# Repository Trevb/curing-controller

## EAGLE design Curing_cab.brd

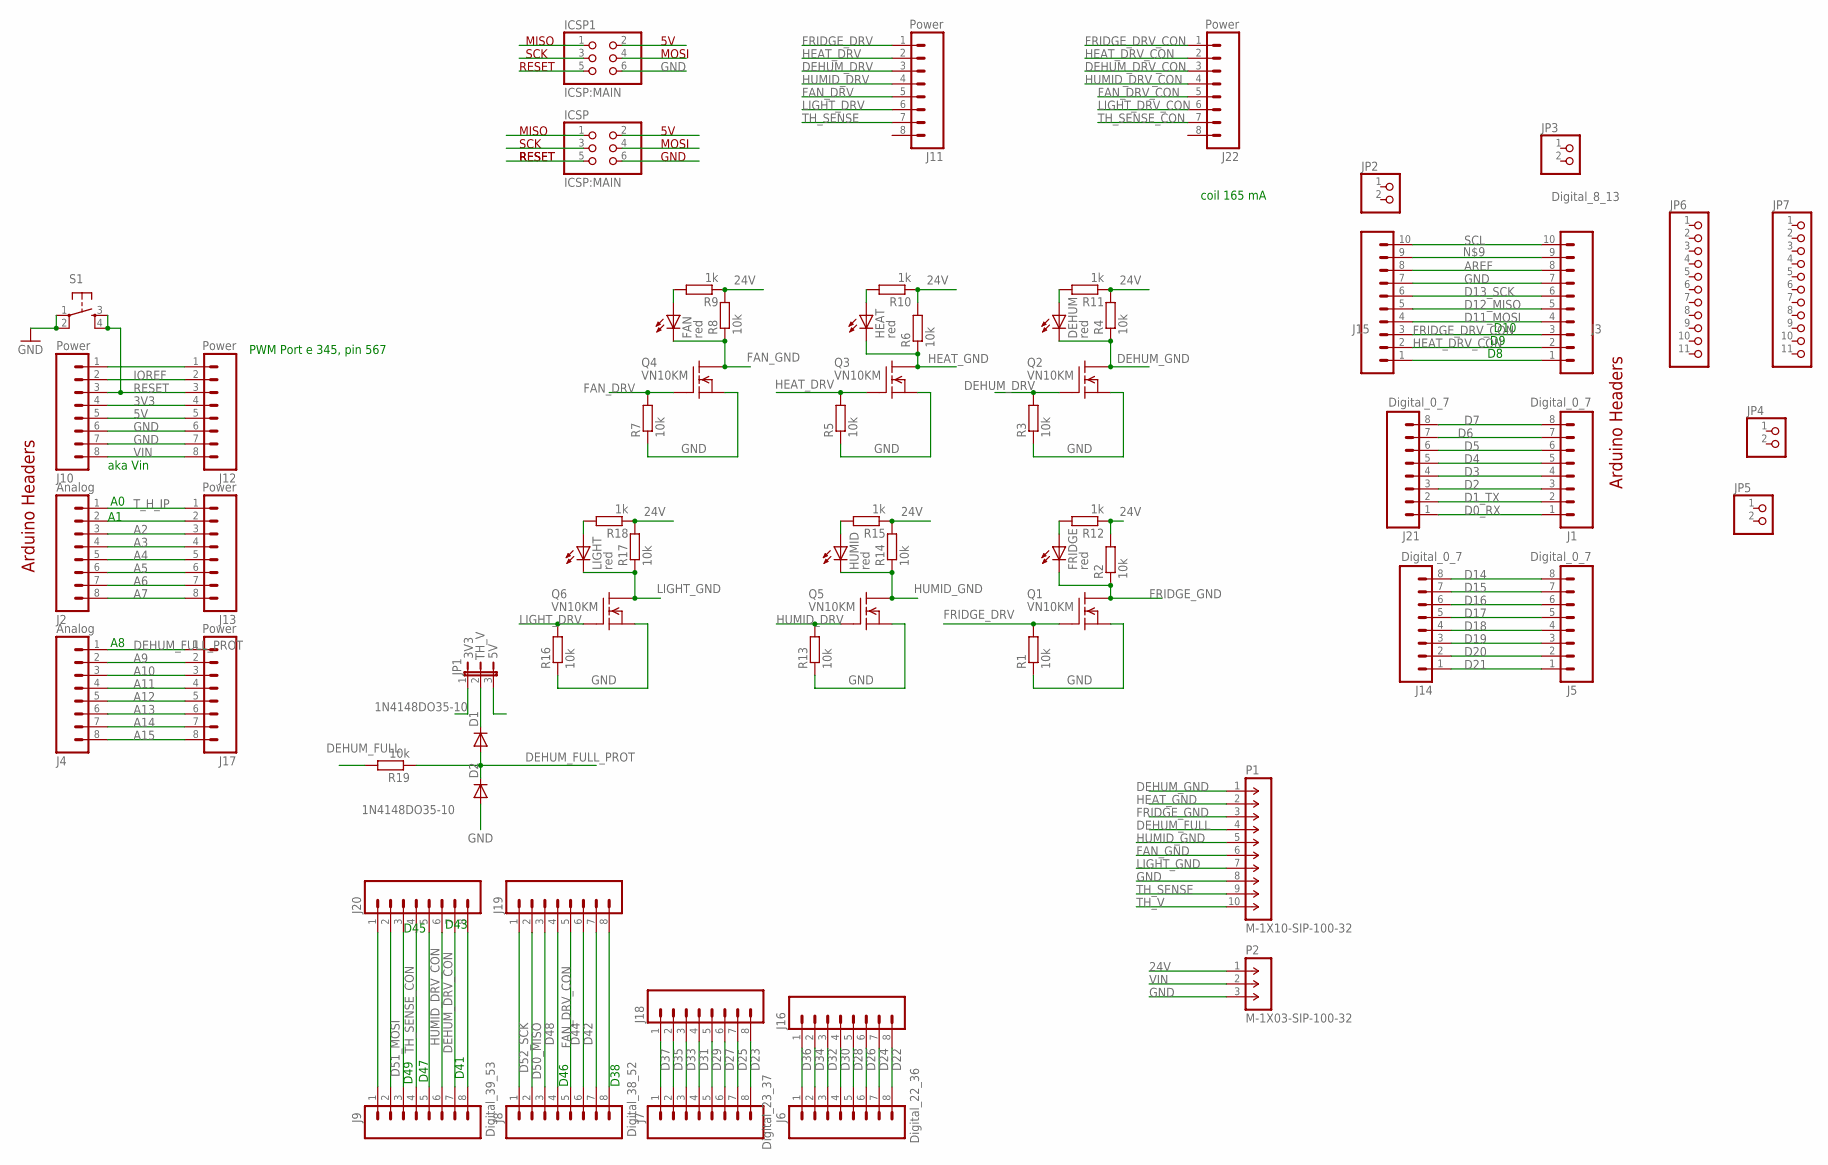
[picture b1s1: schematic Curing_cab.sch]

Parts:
D1, D2: 1N4148DO35-10; DO35-10
DEHUM: red; LED3MM
FAN: red; LED3MM
FRIDGE: red; LED3MM
HEAT: red; LED3MM
HUMID: red; LED3MM
ICSP, ICSP1: ICSP:MAIN; 2X03
J1, J5, J14, J21: Digital_0_7; 1X08
J2, J4: Analog; 1X08
J3, J15: Digital_8_13; 1X10
J6, J16, J18, J19, J20: Digital_22_36; 1X08
J7: Digital_23_37; 1X08
J8: Digital_38_52; 1X08
J9: Digital_39_53; 1X08
J10, J11, J12, J13, J17, J22: Power; 1X08
JP1: JP2E; JP2
JP2, JP3, JP4, JP5: PINHD-1X2; 1X02
JP6, JP7: PINHD-1X11; 1X11
LIGHT: red; LED3MM
P1: M-1X10-SIP-100-32; SIP-100-10-32
P2: M-1X03-SIP-100-32; SIP-100-03-32
Q1, Q2, Q3, Q4, Q5, Q6: VN10KM; TO237
R1, R2, R3, R4, R5, R6, R7, R8, R13, R14, R16, R17, R19: 10k; 0204/7
R9, R10, R11, R12, R15, R18: 1k; 0204/7
S1: TAC_SWITCHPTH; TACTILE-PTH

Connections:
3V3: J10.4, J12.4, JP1.1
5V: J10.5, J12.5, JP1.3
5V_1: ICSP.2, ICSP1.2
24V: P2.1, R2.2, R4.2, R6.2, R8.2, R9.1, R10.1, R11.1, R12.1, R14.2, R15.1, R17.2, R18.1
A2: J2.3, J13.3
A3: J2.4, J13.4
A4: J2.5, J13.5
A5: J2.6, J13.6
A6: J2.7, J13.7
A7: J2.8, J13.8
A9: J4.2, J17.2
A10: J4.3, J17.3
A11: J4.4, J17.4
A12: J4.5, J17.5
A13: J4.6, J17.6
A14: J4.7, J17.7
A15: J4.8, J17.8
AREF: J3.8, J15.8
D0_RX: J1.1, J21.1
D1_TX: J1.2, J21.2
D2: J1.3, J21.3
D3: J1.4, J21.4
D4: J1.5, J21.5
D5: J1.6, J21.6
D6: J1.7, J21.7
D7: J1.8, J21.8
D11_MOSI: J3.4, J15.4
D12_MISO: J3.5, J15.5
D13_SCK: J3.6, J15.6
D14: J5.8, J14.8
D15: J5.7, J14.7
D16: J5.6, J14.6
D17: J5.5, J14.5
D18: J5.4, J14.4
D19: J5.3, J14.3
D20: J5.2, J14.2
D21: J5.1, J14.1
D22: J6.8, J16.8
D23: J7.8, J18.8
D24: J6.7, J16.7
D25: J7.7, J18.7
D26: J6.6, J16.6
D27: J7.6, J18.6
D28: J6.5, J16.5
D29: J7.5, J18.5
D30: J6.4, J16.4
D31: J7.4, J18.4
D32: J6.3, J16.3
D33: J7.3, J18.3
D34: J6.2, J16.2
D35: J7.2, J18.2
D36: J6.1, J16.1
D37: J7.1, J18.1
D42: J8.6, J19.6
D44: J8.5, J19.5
D48: J8.3, J19.3
D50_MISO: J8.2, J19.2
D51_MOSI: J9.2, J20.2
D52_SCK: J8.1, J19.1
D53: J9.1, J20.1
DEHUM_DRV: J11.3, Q2.2 (G), R3.2
DEHUM_DRV_CON: J9.6, J20.6, J22.3
DEHUM_FULL: P1.4, R19.2
DEHUM_FULL_PROT: D1.A, D2.C, J4.1, J17.1, R19.1
DEHUM_GND: DEHUM.K (C), P1.1, Q2.1 (D), R4.1
FAN_DRV: J11.5, Q4.2 (G), R7.2
FAN_DRV_CON: J8.4, J19.4, J22.5
FAN_GND: FAN.K (C), P1.6, Q4.1 (D), R8.1
FRIDGE_DRV: J11.1, Q1.2 (G), R1.2
FRIDGE_DRV_CON: J3.3, J15.3, J22.1
FRIDGE_GND: FRIDGE.K (C), P1.3, Q1.1 (D), R2.1
GND: D2.A, ICSP.6, ICSP1.6, J3.7, J10.6, J10.7, J12.6, J12.7, J15.7, P1.8, P2.3, Q1.3 (S), Q2.3 (S), Q3.3 (S), Q4.3 (S), Q5.3 (S), Q6.3 (S), R1.1, R3.1, R5.1, R7.1, R13.1, R16.1, S1.1, S1.2
HEAT_DRV: J11.2, Q3.2 (G), R5.2
HEAT_DRV_CON: J3.2, J15.2, J22.2
HEAT_GND: HEAT.K (C), P1.2, Q3.1 (D), R6.1
HUMID_DRV: J11.4, Q5.2 (G), R13.2
HUMID_DRV_CON: J9.5, J20.5, J22.4
HUMID_GND: HUMID.K (C), P1.5, Q5.1 (D), R14.1
IOREF: J10.2, J12.2
LIGHT_DRV: J11.6, Q6.2 (G), R16.2
LIGHT_DRV_CON: J9.4, J20.4, J22.6
LIGHT_GND: LIGHT.K (C), P1.7, Q6.1 (D), R17.1
MISO_1: ICSP.1, ICSP1.1
MOSI_1: ICSP.4, ICSP1.4
unnamed: HUMID.A, R15.2
unnamed: FAN.A, R9.2
unnamed: DEHUM.A, R11.2
unnamed: LIGHT.A, R18.2
unnamed: HEAT.A, R10.2
unnamed: J3.1, J15.1
unnamed: FRIDGE.A, R12.2
unnamed: J3.9, J15.9
unnamed: J2.2, J13.2
unnamed: J9.7, J20.7
unnamed: J9.8, J20.8
unnamed: J8.8, J19.8
unnamed: J8.7, J19.7
unnamed: J10.1, J12.1
RESET: J10.3, J12.3, S1.3, S1.4
RESET_1: ICSP.5, ICSP1.5
SCK_1: ICSP.3, ICSP1.3
SCL: J3.10, J15.10
TH_SENSE: J11.7, P1.9
TH_SENSE_CON: J9.3, J20.3, J22.7
TH_V: D1.C, JP1.2, P1.10
T_H_IP: J2.1, J13.1
VIN: J10.8, J12.8, P2.2

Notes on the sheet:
Arduino Headers
GND
MISO
RESET
SCK
MOSI
aka Vin
coil 165 mA
PWM Port e 345, pin 567
D10
D45
D41
D38
D47
D43
D49
D46

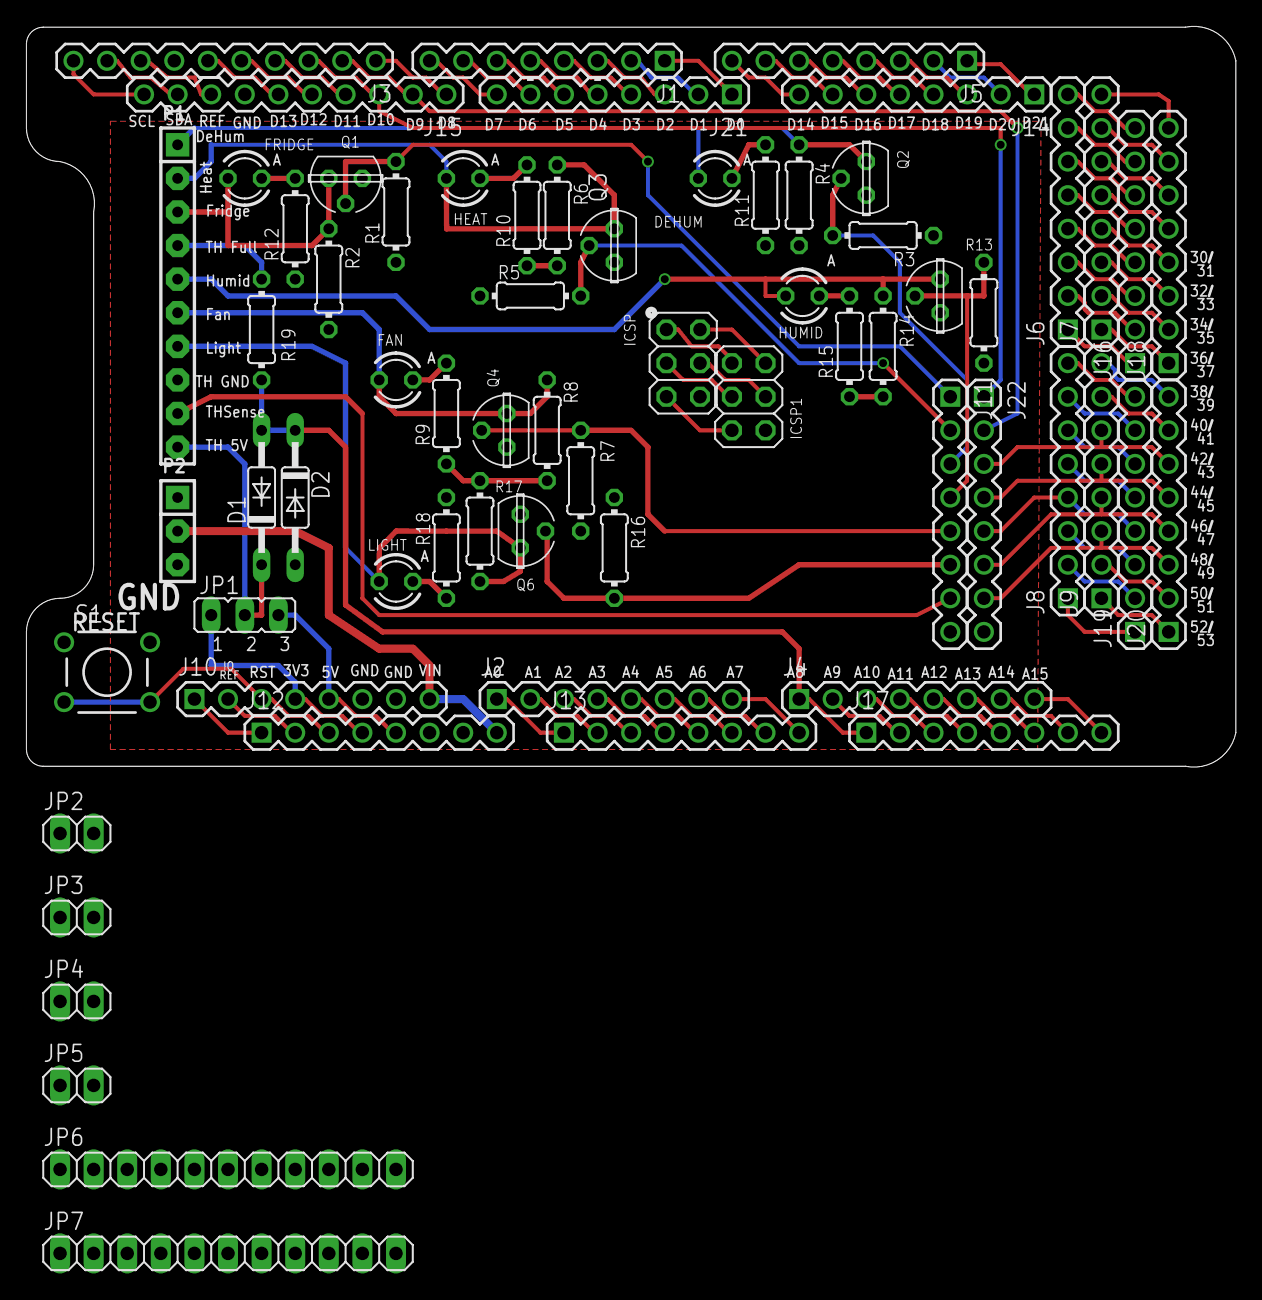
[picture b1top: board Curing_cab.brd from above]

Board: 2 copper layers, 91.4 x 56.0 mm, 67 parts (0 on the bottom side), 107 nets.

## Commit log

2018-07-05 Add files via upload
    prior to extra gnd and and VCC on dual row, and enlarged holes for main connector

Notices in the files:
Curing_cab.brd:
Copyright Pending
parts and their libraries:
con-headers-jp: Copyright (C) 2008, Bob Starr
